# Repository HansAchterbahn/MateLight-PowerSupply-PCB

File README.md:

# MateLight-PowerSupply

## Idea

My MateLight project is based on the idea of [jaseg's MateLight](https://github.com/jaseg/matelight) and improves it with a APA102 LED screw cap PCB which is easy to install and easy to remove from the coasters. An overview about my MateLight project you can find on my [MateLight overview page](https://github.com/HansAchterbahn/MateLightScrewCap-PowerSupply).

## This Repo

In this Repository you can find the power distributor for the MateLight coasters (containing 20 bottles).

You can find following details:
- PCB schematics and board layouts (created in Kicad),
- PCB Gerber data (ready for manufacturing),
- a bill of material (with device ordering numbers) and
- a 3D model of the PCB.

*Fork me and have fun!*

## Power source

An APA102C LED consumes a maximum of 60 mA (red/green/blue each 20 mA). Because of that scince v0.2.0 every screw cap has its own power supply. To connect the power supply of every screw cap in a crate you need the power distributor in this repo.

```
                  LED1                                                   LED19                                   LED20
                 (APA102)                                               (APA102)                                (APA102)
                ----------                                             ----------                              ----------
     .--. Clock |   __   | Clock .--.                       .--. Clock |   __   | Clock .--.        .--. Clock |   __   | Clock .--.
     |  |--->---|  /  \  |---> --|  |                       |  |--->---|  /  \  |--->---|  |        |  |--->---|  /  \  |--->---|  |
     |  | Data  | (    ) | Data  |  |          ooo          |  | Data  | (    ) | Data  |  |        |  | Data  | (    ) | Data  |  |
     |  |--->---|  \__/  |--->---|  |                       |  |--->---|  \__/  |--->---|  |        |  |--->---|  \__/  |--->---|  |
     '--'       |        |       '--'                       '--'       |        |       '--'        '--'       |        |       '--'
                ----------                                             ----------                              ---------|
    Input          |  |         Output                     Input          |  |         Output      Input          |  |         Output
  Connector     5V |  | GND    Connector                 Connector     5V |  | GND    Connector  Connector     5V |  | GND    Connector
                  .----.                                                 .----.                                  .----.
                  |    |                                                 |    |                                  |    |
                  '----'                                                 '----'                                  '----'
                  Power                                                  Power                                   Power
                 Connector                                              Connector                               Connector
```

## PCB 3D view

Animated 3D STL model: [kibot/3d/model](https://github.com/HansAchterbahn/MateLightScrewCap-PowerSupply/kibot/3d/model)

__Top view__
<!--

__Top view 30°__
-->

__Bottom view__
<!--

__Bottom view 30°__
-->

## Schematic

## Board

__Top view__

__Bottom view__

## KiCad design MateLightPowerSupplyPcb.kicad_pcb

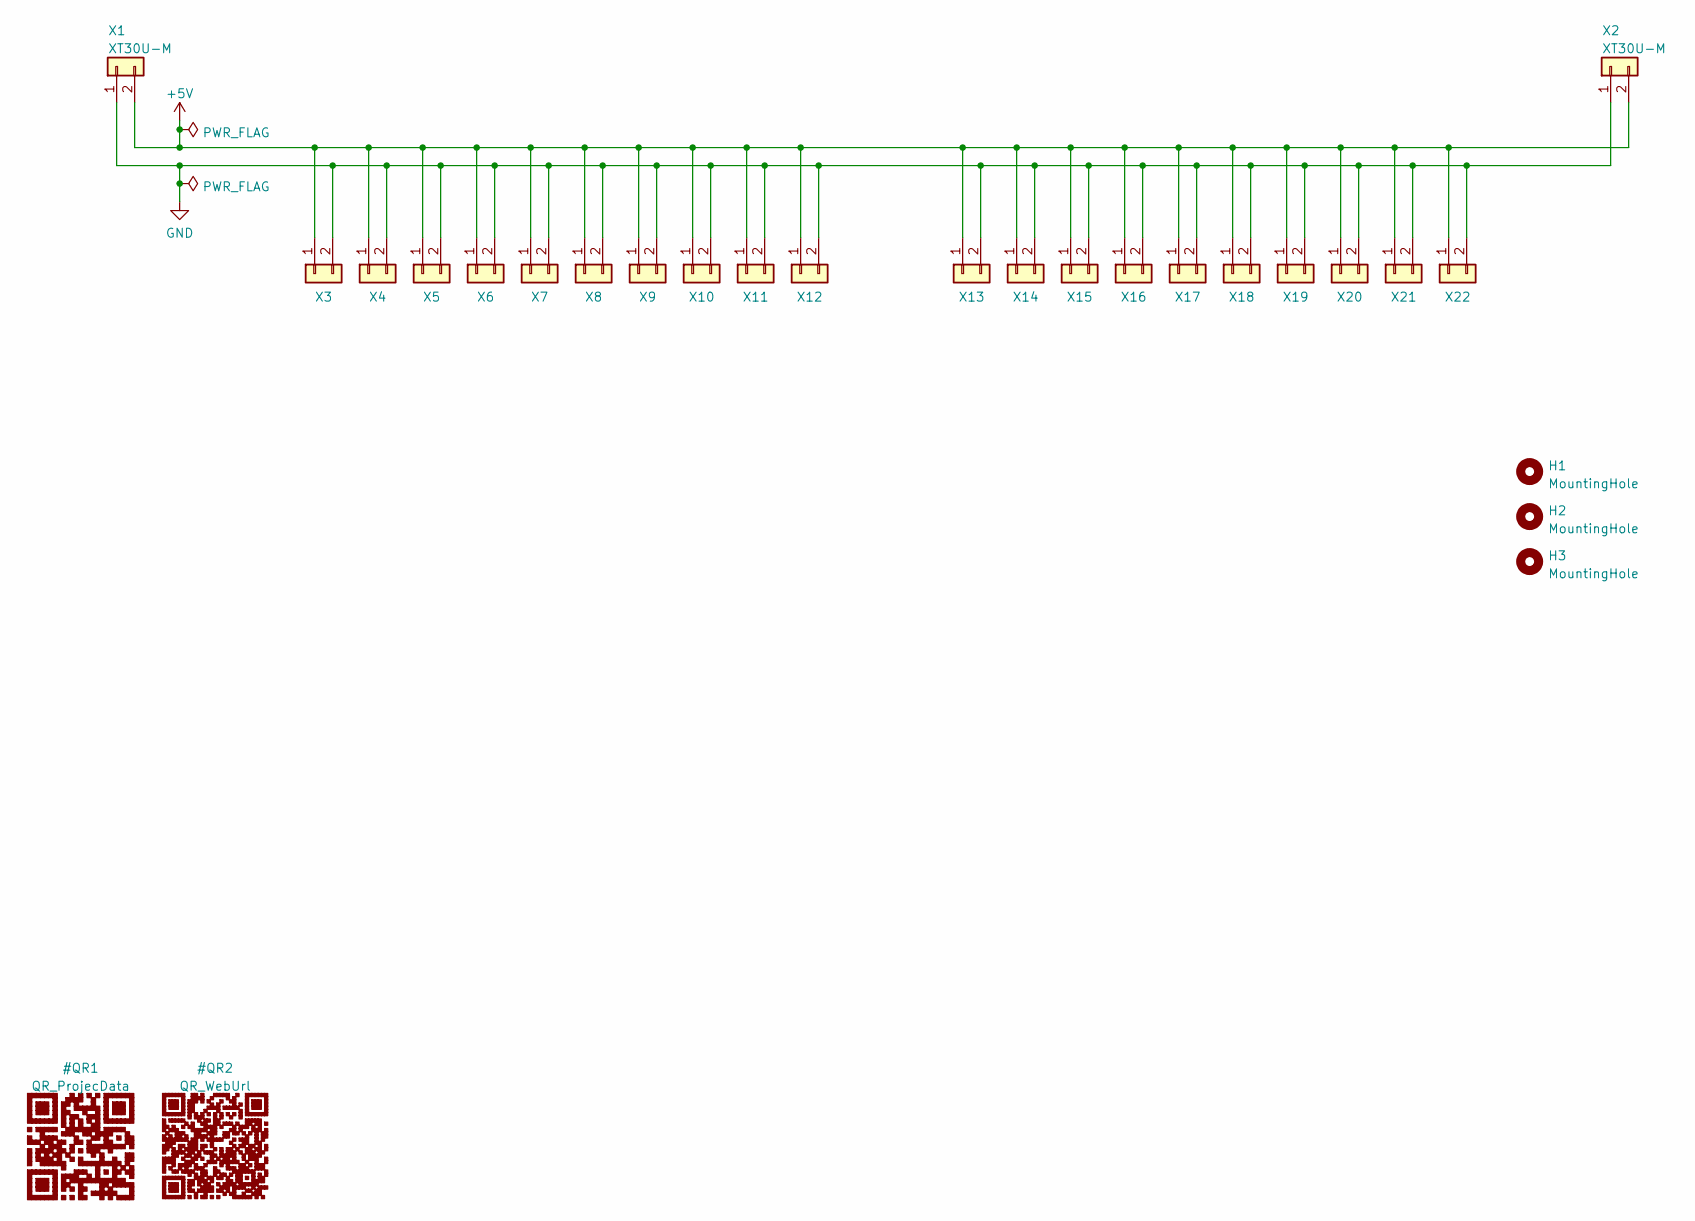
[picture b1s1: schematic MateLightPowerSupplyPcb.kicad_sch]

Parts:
H1, H2, H3: MountingHole; MountingHole_3.2mm_M3_DIN965
X1, X2: XT30U-M; XT30; LCSC# C99101
X3, X4, X5, X6, X7, X8, X9, X10, X11, X12, X13, X14, X15, X16, X17, X18, X19, X20, X21, X22: S2B-ZR-SM4A-TF; JST_S2B-ZR-SM4A-TF(LF)(SN); digi-key 455-1693-1-ND

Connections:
+5V: X1.2, X2.2, X3.1, X4.1, X5.1, X6.1, X7.1, X8.1, X9.1, X10.1, X11.1, X12.1, X13.1, X14.1, X15.1, X16.1, X17.1, X18.1, X19.1, X20.1, X21.1, X22.1
GND: X1.1, X2.1, X3.2, X4.2, X5.2, X6.2, X7.2, X8.2, X9.2, X10.2, X11.2, X12.2, X13.2, X14.2, X15.2, X16.2, X17.2, X18.2, X19.2, X20.2, X21.2, X22.2

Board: 2 copper layers, 27 parts (12 on the bottom side), 2 nets, no tracks yet.

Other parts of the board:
QR1: Project; QR_ProjecData
QR2: WebUrl; QR_WebUrl

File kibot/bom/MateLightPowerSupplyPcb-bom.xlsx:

|  | KiBot Bill of Materials
 |  | Schematic: | MateLightPowerSupplyPcb | Component Groups: | 2
 |  | Variant: | default | Component Count: | 22 (0 SMD/ 22 THT)
 |  | Revision: |  | Fitted Components: | 22 (0 SMD/ 22 THT)
 |  | Date: | 2022-09-29_15-11-03 | Number of PCBs: | 1
 |  | KiCad Version: | 6.0.8-f2edbf62ab~116~ubuntu20.04.1 | Total Components: | 22
Row | Description | Part | References | Value | Footprint | Quantity Per PCB | Status | Datasheet | MF | MFN | digi-key | rs-online | LCSC#
1 | Generic connector, single row, 01x02, script generated (kicad-library-utils/sch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 | Conn_01x02 | X3 X4 X5 X6 X7 X8 X9 X10 X11 X12 X13 X14 X15 X16 X17 X18 X19 X20 X21 X22 | S2B-ZR-SM4A-TF | JST_S2B-ZR-SM4A-TF(LF)(SN) | 20 |  | https://jst.de/file/download/809/zh-connector | JST | S2B-ZR-SM4A-TF | 455-1693-1-ND | 762-0875 | C265329
2 | Generic connector, single row, 01x02, script generated (kicad-library-utils/sch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 | Conn_01x02 | X1 X2 | XT30U-M | XT30 | 2 |  | https://static.chipdip.ru/lib/509/DOC001509847.pdf | AMASS | XT30U-M |  | 180-5359 | C99101

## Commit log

2022-09-17 First draft
2022-09-18 Added mounting options to PCB
2022-09-18 Changed JST ZE to ZR connectors | added 3D models
2022-09-19 Improvements to fit PCB to ZR/ZH connector
2022-09-20 Added description and logos to silkscreen
2022-09-20 Changed some output job settings
2022-09-20 Added outputs: gerber
2022-09-20 Added outputs: prints of board top and bottom view
2022-09-20 Added outputs: 3D model (STEP)
2022-09-21 Changed board page to simply just fit the pcb
2022-09-27 sync: schematic → board
2022-09-27 board: changed draft size to board size
2022-09-29 Added some attributes to parts
2022-09-29 [WIP] Added a first draft of a KiBot basic YAML script
2022-10-01 [WIP] First run with KiBot script "basic-export.kibot.yaml"
2022-10-01 [WIP] KiBot: removed generation of "Schematic Plot (SVG" → unknown Problem
2022-10-01 [WIP] Added QR code and some lables to board and schematic
2022-10-01 [WIP] Added manual rendered picture of the board
2022-10-03 [WIP] Refine and update KiBot Export
2022-10-03 Add README.md
2022-10-04 [WIP] added footprint and symbol table for generated qr-code
2022-10-04 [WIP] Schematic: removed qr-code (keep on pcb), add metadata, update libraries
